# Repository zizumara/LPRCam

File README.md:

# LPRCam

(2022-06-06 NOTE: UCTronics has modified the design of the Arducam 12.3 MP HQ camera with automatic IR-cut filter.  The new design requires the Bullseye O/S to be used, and the IR-cut filter interface now works differently.  Unfortunately, there isn't a distribution of openalpr for Bullseye.  You may be able to special order the older version of the camera from Arducam and continue to use Buster.  If anyone can figure out how to get this project updated for Bullseye, I'd like to hear from them.)

This project includes the software and hardware design for a DIY motion-activated Raspberry Pi security camera.  The Linux Motion application is used to detect motion and capture images.  The following hardware is used for this project:
* Raspberry Pi Zero W running Buster O/S
* Pi Zero W 6" camera ribbon cable (Amazon)
* Raspberry Pi 4 (for web server)
* Arducam 12.3 MP HQ camera with automatic IR-cut filter (www.arducam.com) -- photocell removed
* Arducam 12mm CS-Mount Lens with Manual Focus and Adjustable Aperture (Amazon)
* A custom IR illuminator (KiCAD files included)
* A custom ambient light sensor (KiCAD files included)
* A 3D-printable enclosure (STL files included) -- use white PETG filament
* A 5V 2.5A step-down voltage regulator (Pololu #2858)
* 2.1mm DC panel mount barrel jack (Adafruit #610) and plug
* CESFONJER Mini Locking Toggle Switch (Amazon)
* GIVERARE Combination Travel Cable Lock (Amazon)
* DEWENWILS 60W Outdoor Low Voltage Transformer (Amazon)
* Woods 55213143 16/2 Low Voltage Lighting Cable, 100-Feet (Amazon)
* Red and green LEDs with 330 Ohm current limiting resistors
* 26 AWG wiring with various Dupont connectors (KiCAD files included)
* Clear Lexan sheet 0.08x7.6x11 inch or similar dimensions (Amazon)
* Clear silicone waterproof sealant (Amazon)
* Silicone modified conformal coating (Amazon)
* 22 #3-48x1/2" steel screws (Fastenal or McMaster-Carr)
* 12 #3-48x1/16" steel screws  (Fastenal or McMaster-Carr)
* Microchip Pickit 4 programmer (for programming the custom light sensor)
* (Optional) Wireless Access Point (Amazon)

For nighttime operation, when the ambient light sensor registers light below a configured level, software enables the IR illuminator and switches in the IR-cut filter on the camera module.  The light level is used to select one of three different Motion configuration files which have mmalcam_control_params settings appropriate for daytime, twilight, and nighttime operation, respectively.  The light level is a time-averaged reading for which the width of the sampling window may be adjusted via the sensor I2C interface.

The camera box should be printed with white PETG filament to resist outdoor heat as well as heat generated by the IR illuminator and Pi Zero W.  All parts of the box should be given four coats of silicone modified conformal coating, both inside and out.  (WARNING: silicone modified conformal coating must be applied in an area with good ventilation.)  The Lexan covers for the camera shroud and IR array opening must be cut to fit from the Lexan sheet.  All seams must be filled with silicone sealant to produce a waterproof enclosure, including around the power jack.

# Web Server

The files included in the /web directory provide everything needed to create a web server for reviewing captured images and license plate numbers.  The web server runs on a separate Raspberry Pi 4B.  If the web server is to be accessible from the Internet, it is strongly recommended that the security hardening procedures be followed in setup.txt.

During operation, captured files are periodically copied from the Pi Zero W to the web server via rsync.  A wireless access point may be needed if the camera box is not close to your wireless router.  The web server performs the CPU-intensive analysis of the captured images using OpenALPR to detect and read license plates.  The results are displayed on the web page, an example of which is shown below (for security reasons, plate numbers and actual camera location are blanked out in grey).

For each captured image, a thumbnail is displayed with the date and time of capture and the lighting level at the bottom in format s###, where s is 'd' for day, 't' for day-twilight, 'u' for night-twilight, and 
'n' for night, and the 3-digit number represents the value read from the light sensor.  If a plate is detected by OpenALPR, the highest confidence plate number result is displayed below the capture date, along with the best confidence level of the optical character recognition (OCR) algorithm (0-100%).  A question mark (?) follows the plate number as a signal that this is the best guess by OpenALPR.  Users may click on any thumbnail to display the full resolution image on a new page.  On this page, the user may enter the actual license plate number so that it may be displayed on the main page in green followed by the text "** verified **".

The top of the main page has a filter section which may be used to limit the number of images displayed.

* Starting date: By default, all captured images are displayed regardless of capture date.  Setting the date and clicking Apply Filters can be used to limit the list to more recent images.
* Search for license: Enter license plate text in this box and click Apply Filters to find OpenALPR results similar to the text supplied.  Use the match strength radio buttons to set how close the match must be to the supplied text.
* Show only detected plates: Check this box and click Apply Filters to display only images for which OpenALPR has found a license plate.

The license plate search algorithm is optimized using OCR statistics gathered from hundreds of prior OpenALPR results that were each manually verified on the view full image page.  Entries made here are added to the OpenALPR .json files in the results directory.  Certain characters like 'B' may be misinterpreted by the OCR engine as '8', or 'D' may be misinterpreted as '4'.  Some characters, like 'I' may not be present at all on any license plate, but might be misidentified from a '1' or from an edge on the license plate.  The genalprstats.py module analyzes the contents of the results directory to determine the frequency at which characters are correctly or incorrectly identified.  The results of this analysis are stored in ocrstats.pickle and applied when the user performs a license plate search using a modified Wagner-Fischer algorithm to find the Levenshtein distance between the plate number entered and the plate numbers returned by OpenALPR.

The Levenshtein distance is defined as the smallest number of 1-character substitutions to convert one string into another.  The modifications to the Wagner-Fischer algorithm allow for the substitution value (normally 1) to be less than one depending on the frequency at which the OCR engine makes an error for the particular substitution. This modified Levenshtein distance can be set as the threshold to count an OpenALPR result as as match when performing a search.  The threshold for the search can be set using the radio buttons at the top of the main web page.  A modified Levenshtein distance of 3.0 or greater signifies a "weak" match, while a modified Levenshtein distance of 1.0 or less represents a "stong" match.

The ocrstats.pickle file in this archive are specific to the location at which testing was originally performed.  This may not be suitable for a different location, in which case a new file might be generated.  However, keep in mind that this requires a large number of plates to be manually verified to generate sufficient data for the analysis.  The existing ocrstats.pickle file was generated from approximately 1,000 analyzed plates, and a similar number is recommended for a new analysis.

# Performance

The following factors are the most significant in their effect on the performance of this system.

* Motion frame rate: The Motion application can capture about 1 to 2 frames per second under the given configuration.  This depends on image size and the processing power of the Raspberry Pi Zero W.  The current frame rate appears to be suitable for capturing at least one image of a license plate on a moving vehicle under most conditions.  The frame rate could be increased by reducing the image size or replacing the Pi Zero W with a Pi Zero 2 W.  However, increasing the rate at which images are captured may be detrimental to other performance factors.
* Image capture rate: The Motion application may experience false positives for detecting motion due to changing lighting conditions.  In particular, windy, partly cloudy days often produce hundreds or even thousands of additional images per day, as the changing cloud shadows often cause significant numbers of pixels in the image to change intensity.  The threshold parameter in motion_day.conf sets the number of changed pixels to trigger motion capture.
* Image transfer rate: Images are periodically transferred from the camera system to the web server for OpenALPR analysis using rsync.  If the image capture rate is large for an extended period, this can generate a large backlog of images to transfer, depending on the configured number of days to keep images in LPRCam.conf.  The result may be that the web server gets behind by several hours in analyzing images.  To reduce the number of image files to be synchronized, keep the number of days to keep files in LPRCam.conf low (no more than 1.0 days).  Note that the web server will keep images for three days, which is hardcoded in LPRserver.py.  The rsync bwlimit parameter is also hardcoded in LPRserver.py at 400 kbps to avoid overloading the wireless network, but may be increased or eliminated.
* ALPR masks: A portion of each image may be excluded from analysis by the OpenALPR application to reduce processing time for each image as defined by mask files.  Two mask files are provided in this archive, alpr-mask-1600x960.jpg and alpr-mask-800x480.jpg, which mask out the lower portion of the image where license plates are not expected to be found.  It may be necessary to replace or exclude these files.  Note that if renamed or excluded, the configuration files openalpr.defaults.1600x960 and openalpr.defaults.800x480 must be updated.
* ALPR processing: OpenALPR consumes considerable CPU resources in analyzing each image, which can result in a significant processing backlog.  Performance can be improved by reducing image dimensions.  Note that this must be done for all the motion configuration files and the OpenALPR mask files.

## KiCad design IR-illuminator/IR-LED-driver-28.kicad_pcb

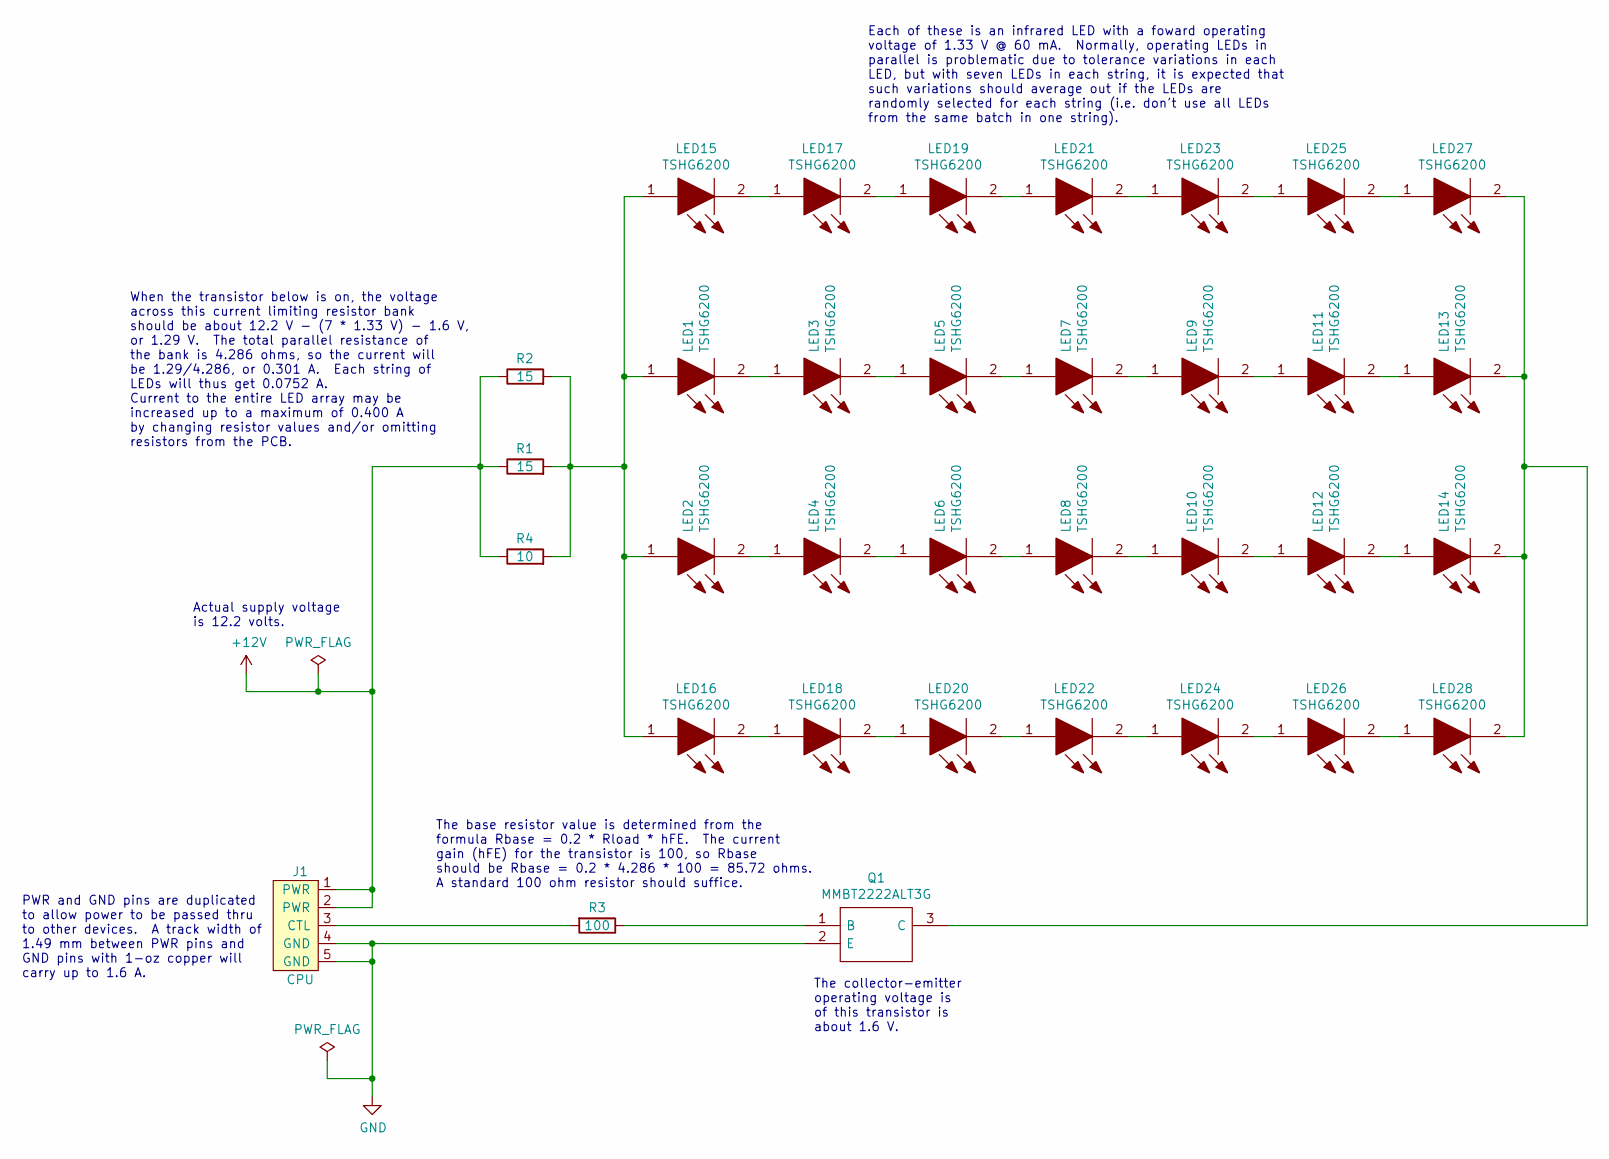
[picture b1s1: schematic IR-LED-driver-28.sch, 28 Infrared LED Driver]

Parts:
J1: CPU; PinHeader_1x05_P2.54mm_Horiz_SMD
LED1, LED2, LED3, LED4, LED5, LED6, LED7, LED8, LED9, LED10, LED11, LED12, LED13, LED14, LED15, LED16, LED17, LED18, LED19, LED20, LED21, LED22, LED23, LED24, LED25, LED26, LED27, LED28: TSHG6200; Mouser Part Number 782-TSHG6200
Q1: MMBT2222ALT3G; SOT96P237X111-3N; Mouser Part Number 863-MMBT2222ALT3G
R1, R2: 15; R_0805_2012Metric_Pad1.15x1.40mm_HandSolder
R3: 100; R_0805_2012Metric_Pad1.15x1.40mm_HandSolder
R4: 10; R_0805_2012Metric_Pad1.15x1.40mm_HandSolder

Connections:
+12V: J1.1 (PWR), J1.2 (PWR), R1.1, R2.1, R4.1
GND: J1.4 (GND), J1.5 (GND), Q1.2 (E)
unnamed: J1.3 (CTL), R3.2
unnamed: LED1.1, LED2.1, LED15.1, LED16.1, R1.2, R2.2, R4.2
unnamed: LED1.2, LED3.1
unnamed: LED2.2, LED4.1
unnamed: LED3.2, LED5.1
unnamed: LED4.2, LED6.1
unnamed: LED5.2, LED7.1
unnamed: LED6.2, LED8.1
unnamed: LED7.2, LED9.1
unnamed: LED8.2, LED10.1
unnamed: LED10.2, LED12.1
unnamed: LED9.2, LED11.1
unnamed: LED11.2, LED13.1
unnamed: LED12.2, LED14.1
unnamed: LED13.2, LED14.2, LED27.2, LED28.2, Q1.3 (C)
unnamed: LED15.2, LED17.1
unnamed: LED16.2, LED18.1
unnamed: LED17.2, LED19.1
unnamed: LED18.2, LED20.1
unnamed: LED19.2, LED21.1
unnamed: LED20.2, LED22.1
unnamed: LED21.2, LED23.1
unnamed: LED22.2, LED24.1
unnamed: LED23.2, LED25.1
unnamed: LED24.2, LED26.1
unnamed: LED25.2, LED27.1
unnamed: LED26.2, LED28.1
unnamed: Q1.1 (B), R3.1

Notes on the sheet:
The collector-emitter operating voltage is of this transistor is about 1.6 V.
Each of these is an infrared LED with a foward operating voltage of 1.33 V @ 60 mA. Normally, operating LEDs in parallel is problematic due to tolerance variations in each LED, but with seven LEDs in each string, it is expected that such variations should average out if the LEDs are randomly select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
When the transistor below is on, the voltage across this current limiting resistor bank should be about 12.2 V - (7 * 1.33 V) - 1.6 V, or 1.29 V. The total parallel resistance of the bank is 4.286 ohms, so the current will be 1.29/4.286, or 0.301 A. Each string of LEDs will thus get 0.0752 A. Curre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
Actual supply voltage is 12.2 volts.
The base resistor value is determined from the formula Rbase = 0.2 * Rload * hFE. The current gain (hFE) for the transistor is 100, so Rbase should be Rbase = 0.2 * 4.286 * 100 = 85.72 ohms. A standard 100 ohm resistor should suffice.
PWR and GND pins are duplicated to allow power to be passed thru to other devices. A track width of 1.49 mm between PWR pins and GND pins with 1-oz copper will carry up to 1.6 A.

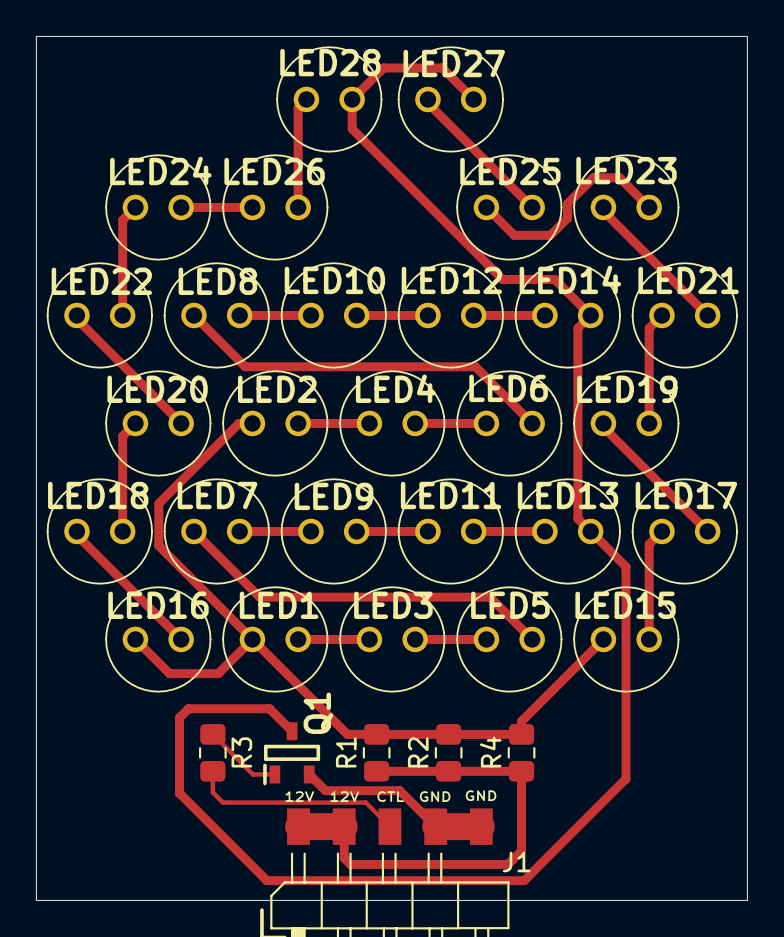
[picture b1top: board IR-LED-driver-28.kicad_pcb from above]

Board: 2 copper layers, 39.5 x 48.0 mm, 34 parts (0 on the bottom side), 30 nets.

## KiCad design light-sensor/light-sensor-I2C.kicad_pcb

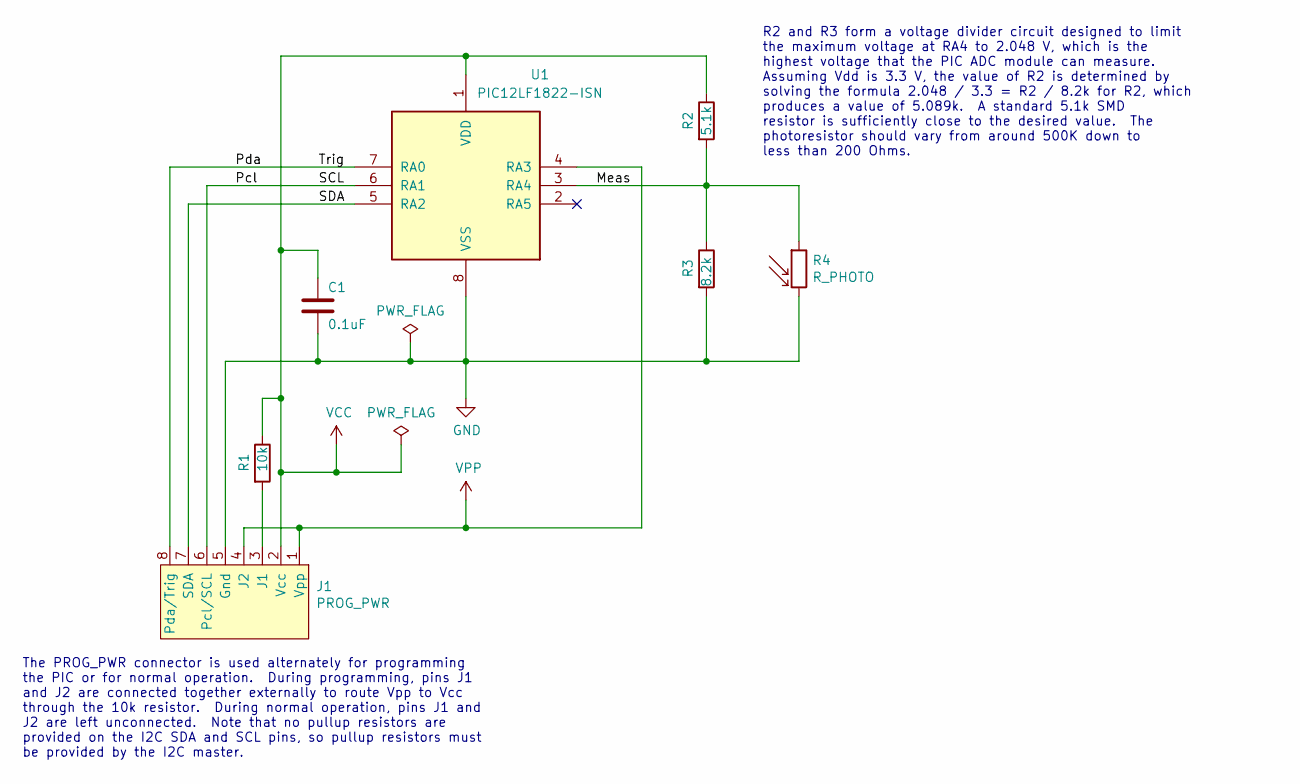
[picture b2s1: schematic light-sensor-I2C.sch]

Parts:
C1: 0.1uF; C_0805_2012Metric_Pad1.15x1.40mm_HandSolder
J1: PROG_PWR; PinSocket_2x04_P2.54mm_Horizontal
R1: 10k; R_0805_2012Metric_Pad1.15x1.40mm_HandSolder
R2: 5.1k; R_0805_2012Metric_Pad1.15x1.40mm_HandSolder
R3: 8.2k; R_0805_2012Metric_Pad1.15x1.40mm_HandSolder
R4: R_PHOTO; R_LDR_7x6mm_P5.1mm_Vertical
U1: PIC12LF1822-ISN; pic12lf1822-i&slash_sn

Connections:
/Meas: R2.2, R3.1, R4.1, U1.3 (RA4)
/Pcl: J1.6 (Pcl/SCL), U1.6 (RA1)
/Pda: J1.8 (Pda/Trig), U1.7 (RA0)
/SDA: J1.7 (SDA), U1.5 (RA2)
GND: C1.2, J1.5 (Gnd), R3.2, R4.2, U1.8 (VSS)
unnamed: J1.3 (J1), R1.2
VCC: C1.1, J1.2 (Vcc), R1.1, R2.1, U1.1 (VDD)
VPP: J1.1 (Vpp), J1.4 (J2), U1.4 (RA3)

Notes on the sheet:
R2 and R3 form a voltage divider circuit designed to limit the maximum voltage at RA4 to 2.048 V, which is the highest voltage that the PIC ADC module can measure. Assuming Vdd is 3.3 V, the value of R2 is determined by solving the formula 2.048 / 3.3 = R2 / 8.2k for R2, which produces a value of 5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
The PROG_PWR connector is used alternately for programming the PIC or for normal operation. During programming, pins J1 and J2 are connected together externally to route Vpp to Vcc through the 10k resistor. During normal operation, pins J1 and J2 are left unconnected. Note that no pullup resistors 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

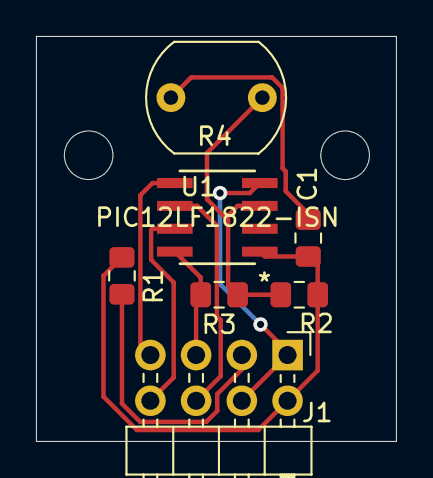
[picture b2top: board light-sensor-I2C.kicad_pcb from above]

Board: 2 copper layers, 20.0 x 22.5 mm, 7 parts (0 on the bottom side), 8 nets.

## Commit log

2022-04-16 Create README.md
    This project includes the software and hardware design for DIY Raspberry Pi based security camera. The Linux Motion application is used to detect motion and capture images, and additional custom hard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
2022-04-21 Add files via upload
    ALPR config files are no longer copied over the default ALPR config. Instead, the --config option is used to point to the correct config file.
    New statistics were added to the LPRserver log file.
    Changed rsync bwlimit from 600 kbps to 400 kbps.
2022-04-23 Add files via upload
    Change keepImageDays from 3 to 1.0 for performance improvement.
2022-04-26 Add files via upload
    Minor logging improvements
2022-05-08 Add files via upload
    Changed motion configuration from three settings (day, twilight, night) to four settings (day, day-twilight, night-twilight, night). Also changed so that latitude and longitude are set via LPRCam.con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
2022-06-06 Update README.md with note about Arducam camera changes and compatibility.
2024-04-20 Added camera focus testing code
2024-04-20 Delete test.py
    Changed my mind. This test code applies to a later version of this project.

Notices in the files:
parts and their libraries:
Copyright 2016 Accelerated Designs. All rights reserved.
